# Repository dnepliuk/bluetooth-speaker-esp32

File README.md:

# bluetooth-speaker-esp32

Двошарова плата Bluetooth-колонки на ESP32, з ЦАП PCM5102A і підсилювачем TPA3116D2.

Відкрийте `BluetoothSpeaker.kicad_pro` у KiCad 10 зі стандартними бібліотеками символів, посадкових місць і 3D-моделей. Локальні бібліотеки зберігаються в `lib/`. Таблиці `sym-lib-table` та `fp-lib-table` посилаються на них відносно папки проєкту. Правила плати містяться в `BluetoothSpeaker.kicad_dru`.

Для механічного компонування доступна модель корпусу U7 у `lib/ul_TPA3116D2DAD/DAD0032A.stp`. PCB посилається на стандартні моделі KiCad для U7 та клемників J1/J3/J4. Якщо цих моделей немає в установленому наборі, відповідні корпуси можуть не відображатися у 3D.

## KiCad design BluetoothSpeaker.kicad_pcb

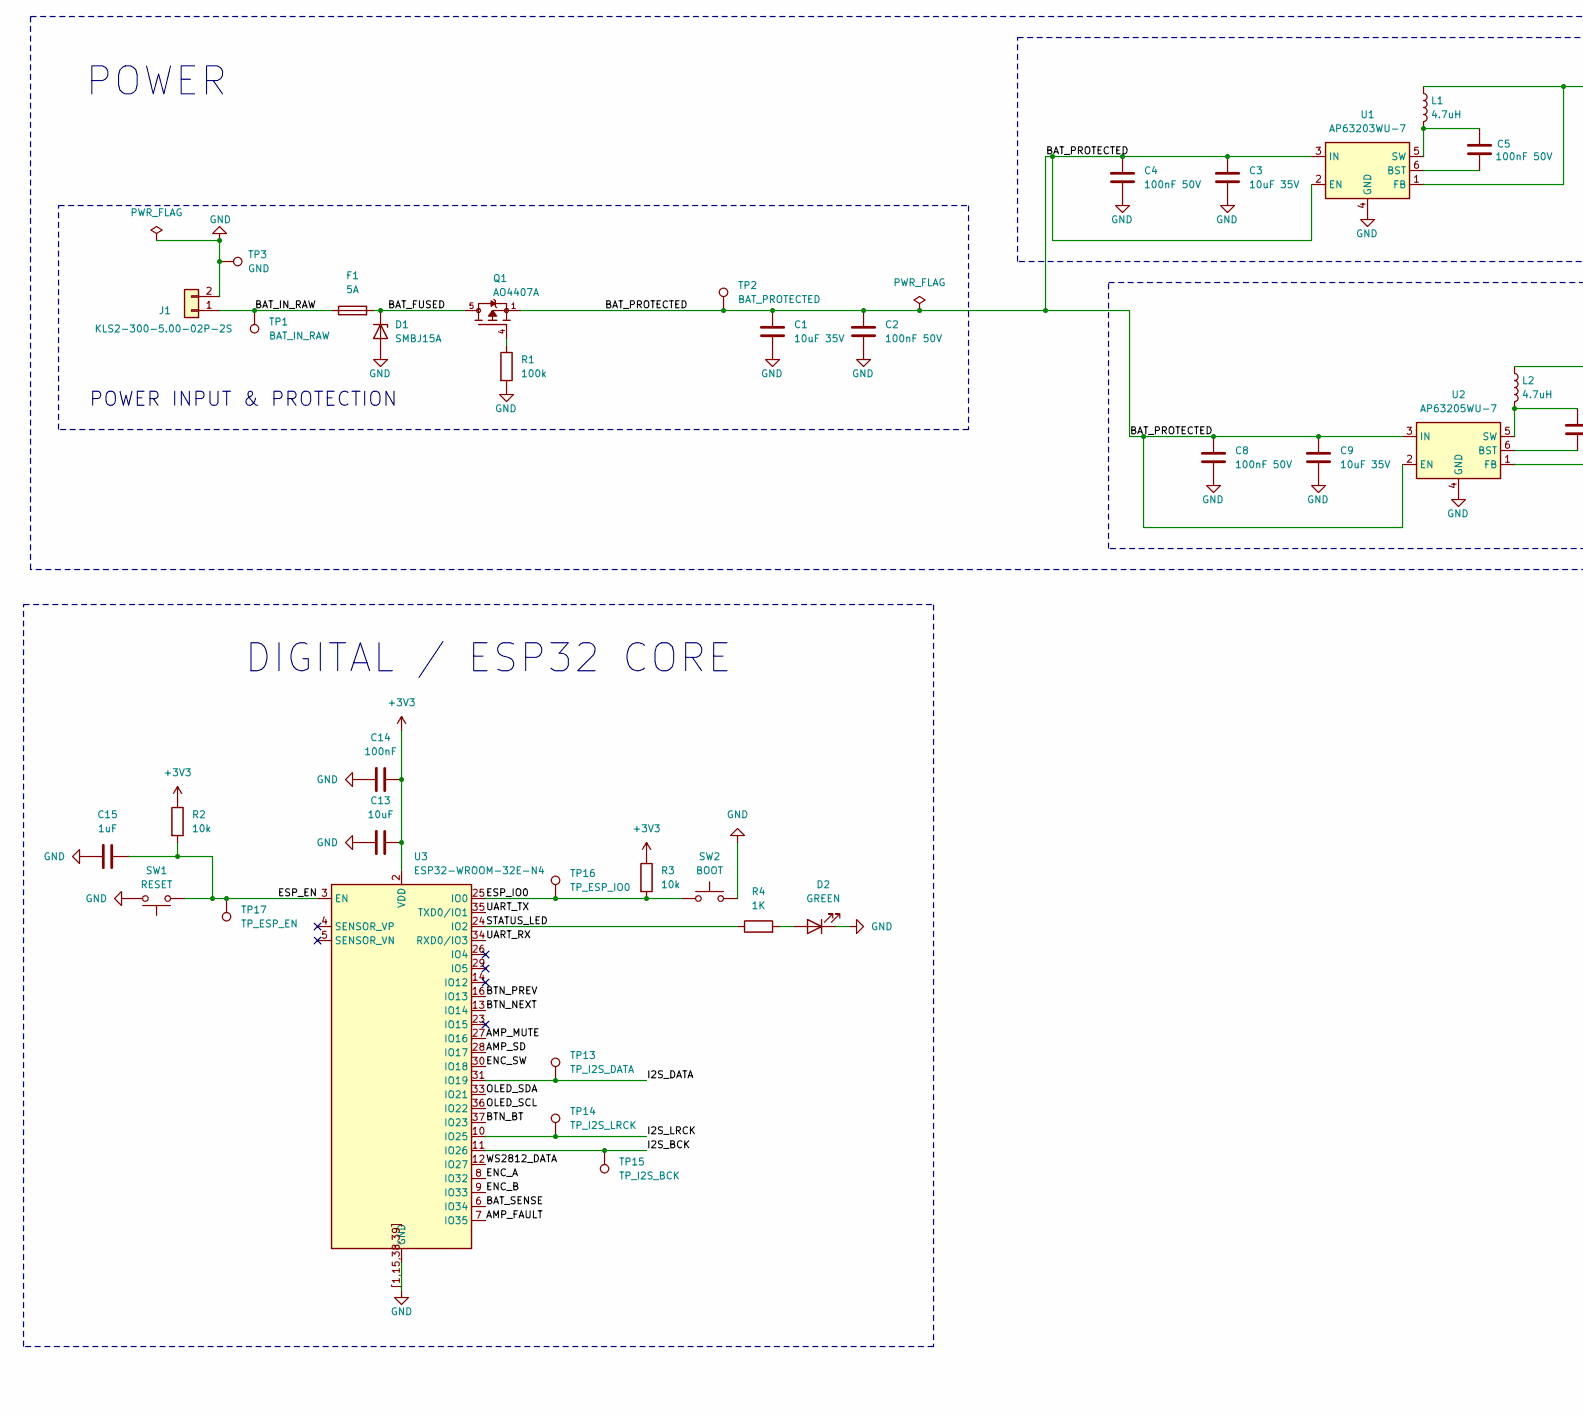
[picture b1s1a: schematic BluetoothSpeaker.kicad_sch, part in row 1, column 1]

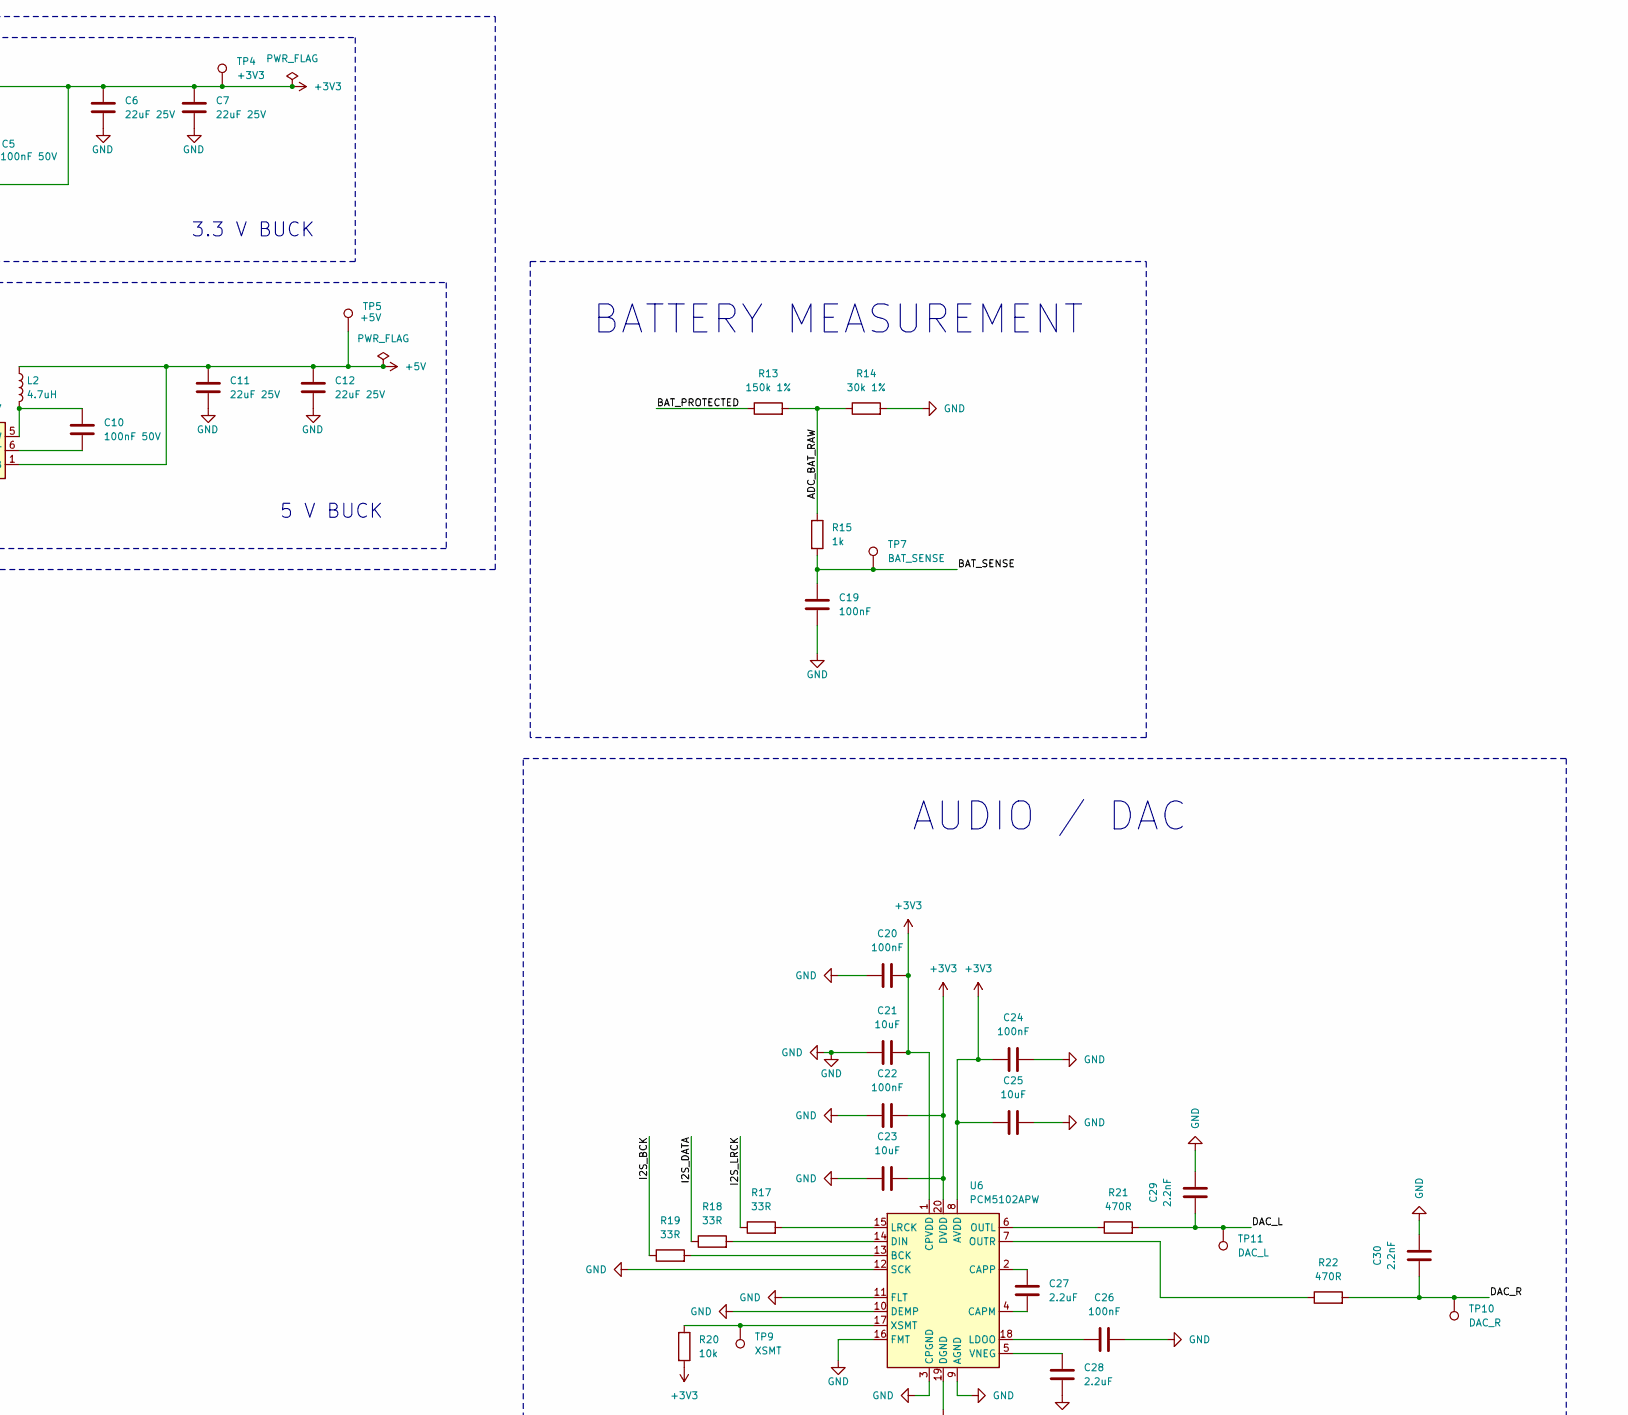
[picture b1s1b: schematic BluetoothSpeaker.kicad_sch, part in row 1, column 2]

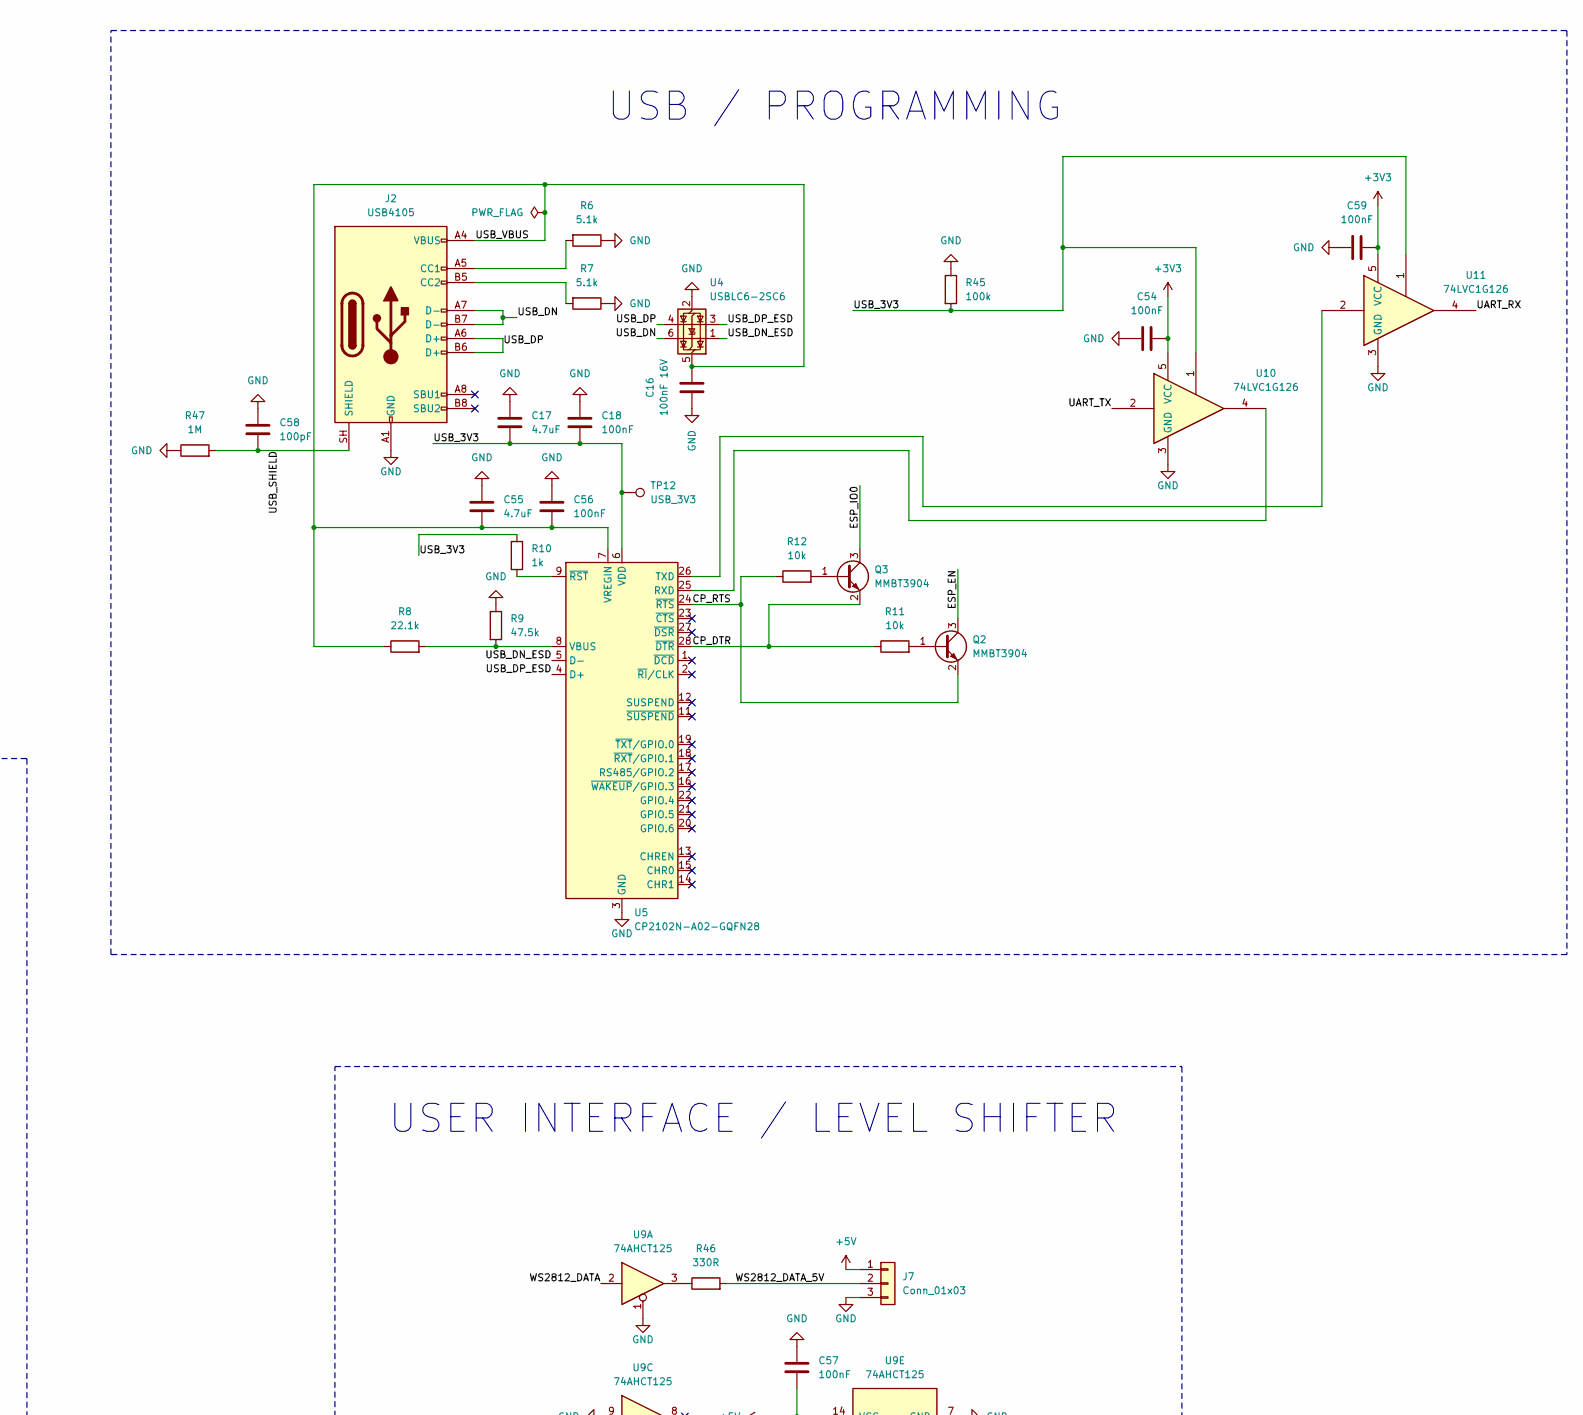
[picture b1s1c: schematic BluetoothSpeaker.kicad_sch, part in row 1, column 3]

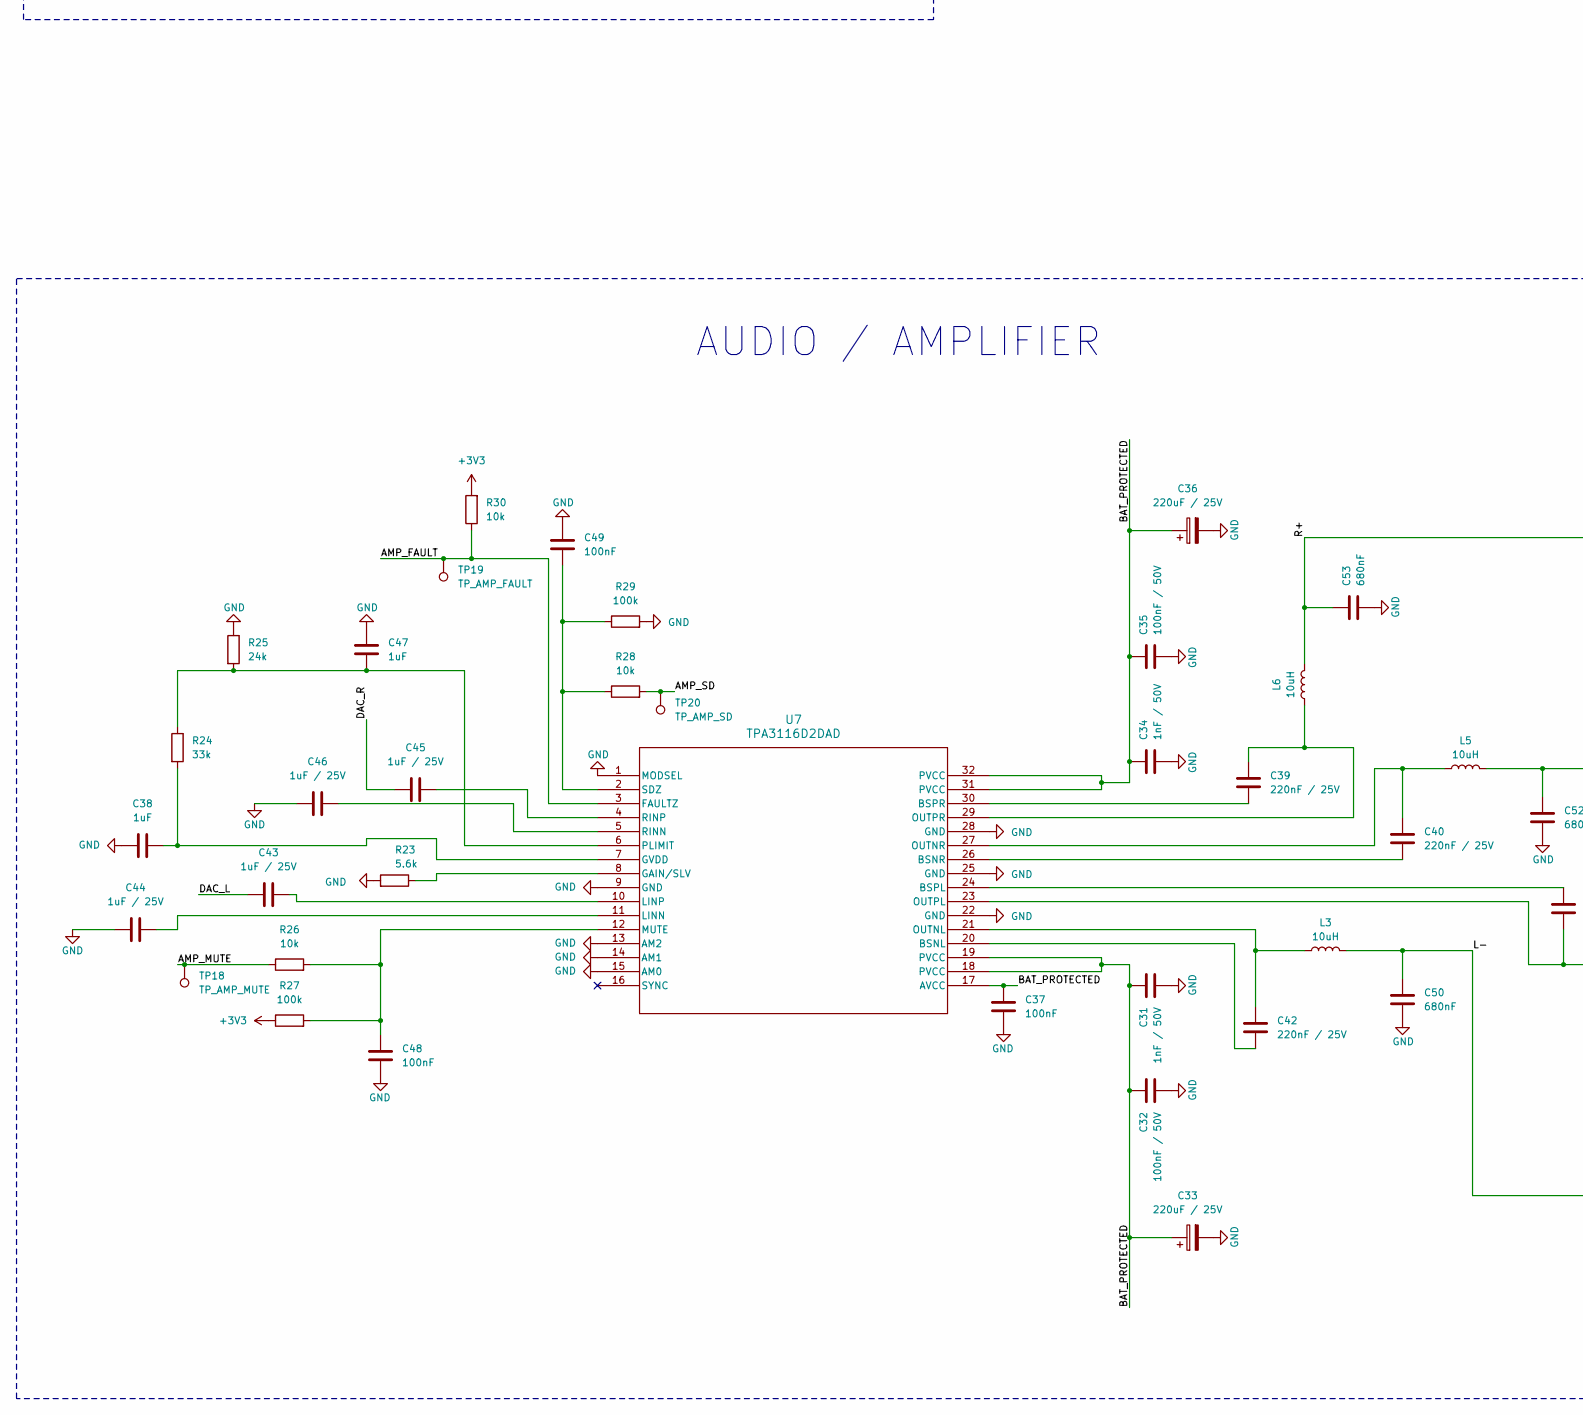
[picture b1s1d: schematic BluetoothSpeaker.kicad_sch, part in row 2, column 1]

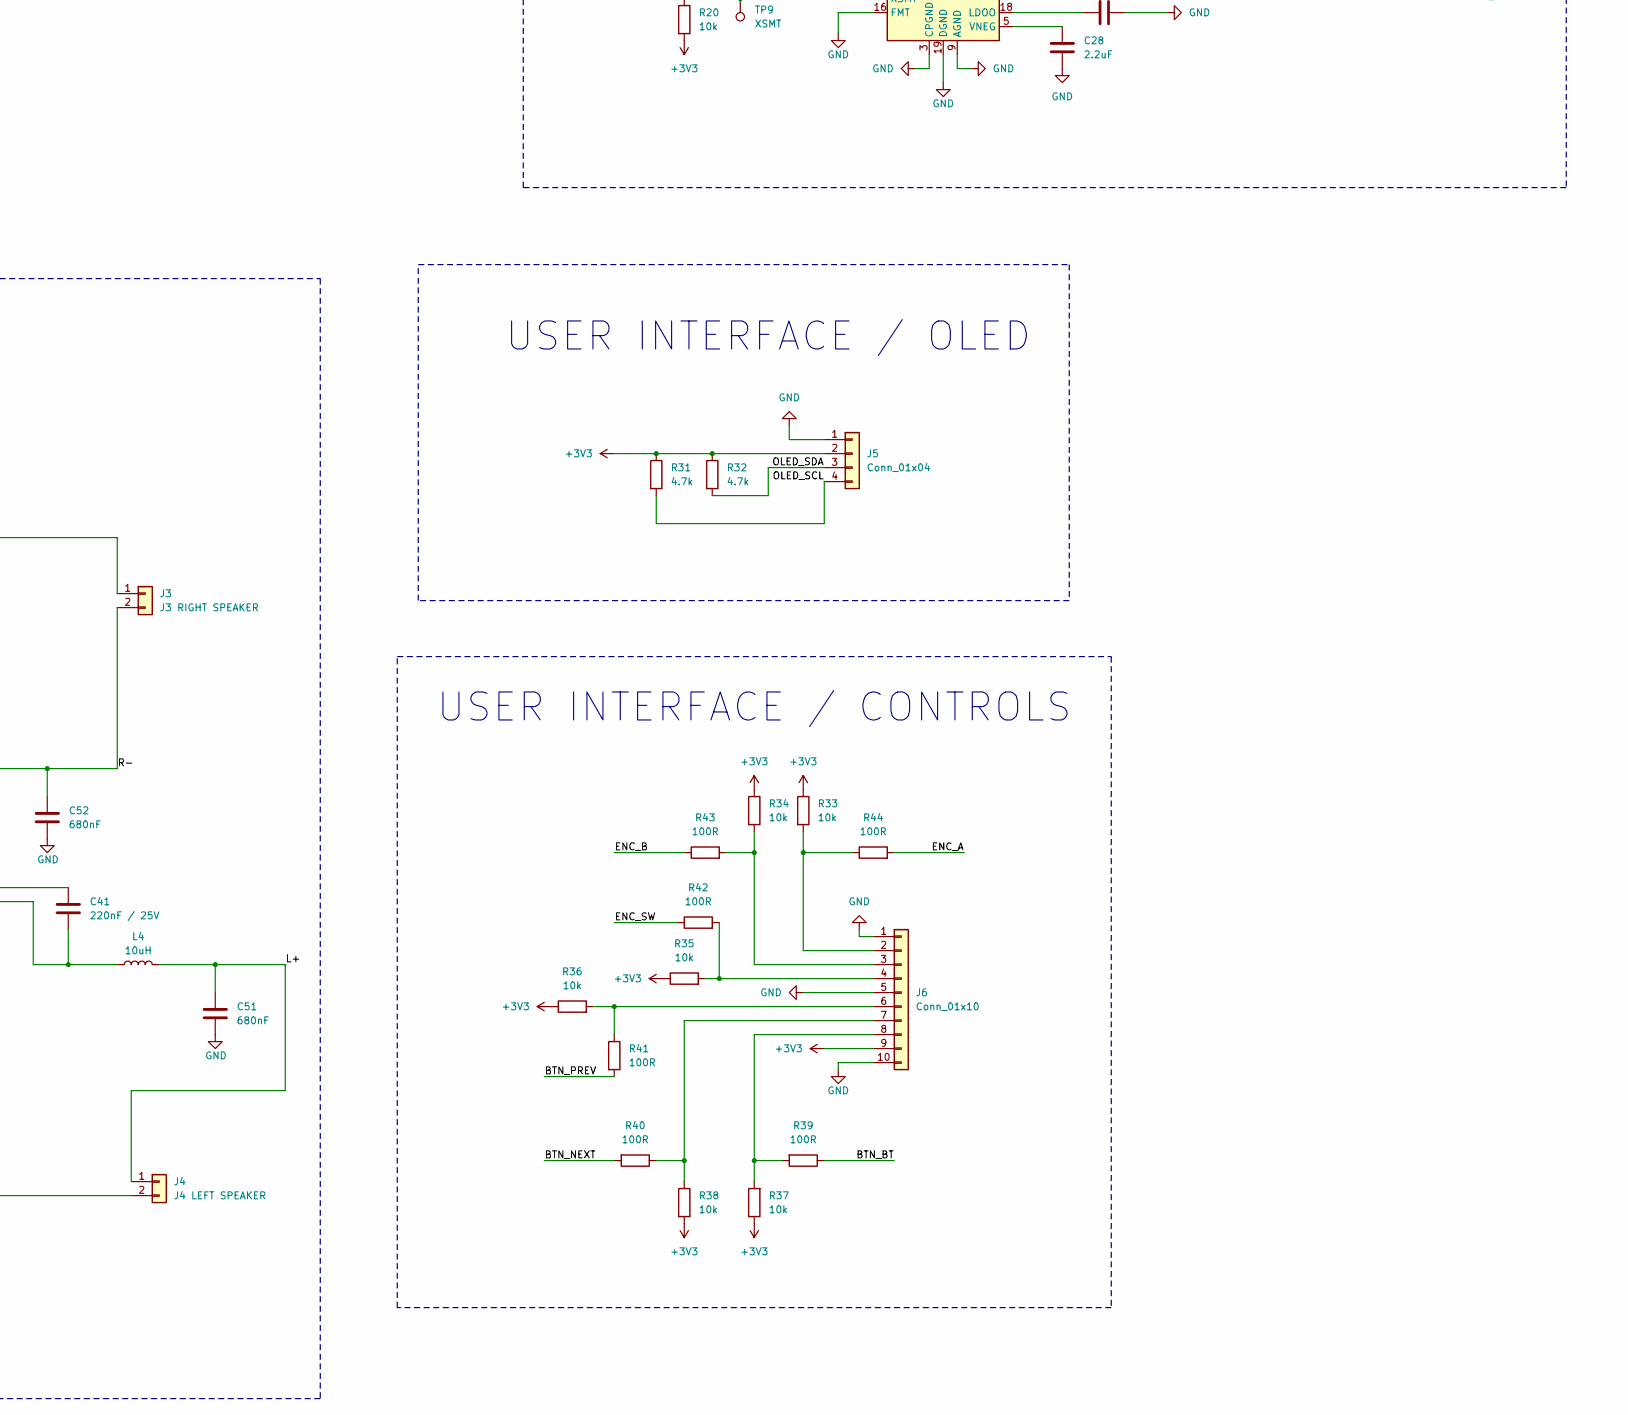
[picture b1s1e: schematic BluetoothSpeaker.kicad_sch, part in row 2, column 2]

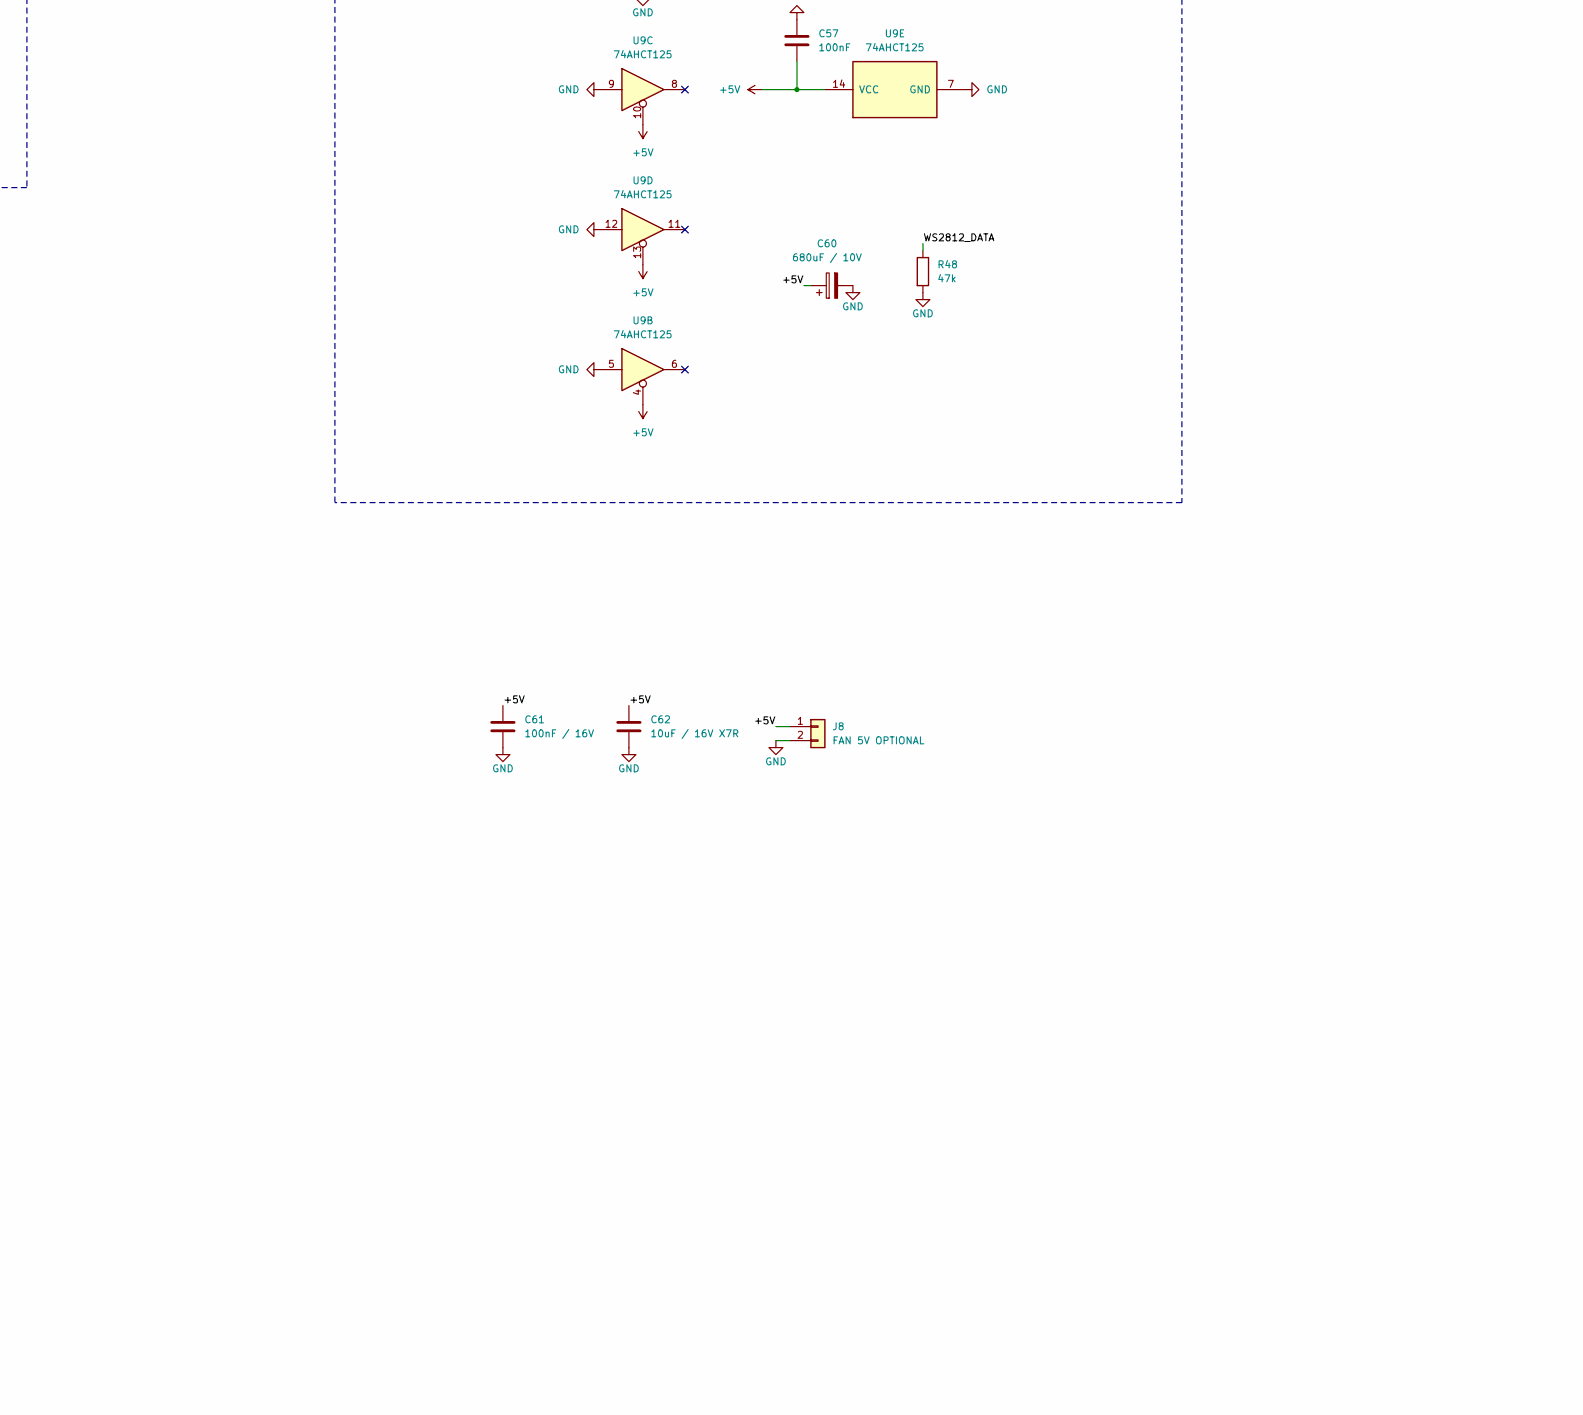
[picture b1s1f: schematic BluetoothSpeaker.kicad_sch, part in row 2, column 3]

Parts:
C1, C3, C9: 10uF 35V; C_1210_3225Metric
C2, C4, C5, C8, C10: 100nF 50V; C_0805_2012Metric
C6, C7, C11, C12: 22uF 25V; C_1210_3225Metric
C13, C21, C23, C25: 10uF; C_1206_3216Metric
C14, C18, C19, C20, C22, C24, C26, C37, C48, C49, C54, C56, C57, C59: 100nF; C_0805_2012Metric
C15, C38, C47: 1uF; C_0805_2012Metric
C16: 100nF 16V; C_0805_2012Metric
C17, C55: 4.7uF; C_0805_2012Metric
C27, C28: 2.2uF; C_0805_2012Metric
C29, C30: 2.2nF; C_0805_2012Metric
C31, C34: 1nF / 50V; C_0805_2012Metric
C32, C35: 100nF / 50V; C_0805_2012Metric
C33, C36: 220uF / 25V; CP_Radial_D8.0mm_P3.50mm
C39, C40, C41, C42: 220nF / 25V; C_0805_2012Metric
C43, C44, C45, C46: 1uF / 25V; C_0805_2012Metric
C50, C51, C52, C53: 680nF; C_1812_4532Metric
C58: 100pF; C_1206_3216Metric
C60: 680uF / 10V; CP_Radial_D8.0mm_P3.50mm
C61: 100nF / 16V; C_0805_2012Metric
C62: 10uF / 16V X7R; C_1206_3216Metric
D1: SMBJ15A; D_SMB
D2: GREEN; LED_0805_2012Metric
F1: 5A; C_1808_4520Metric
J1: KLS2-300-5.00-02P-2S; TerminalBlock_MaiXu_MX126-5.0-02P_1x02_P5.00mm
J2: USB4105; GCT_USB4105_JLC
J3: J3 RIGHT SPEAKER; TerminalBlock_MaiXu_MX126-5.0-02P_1x02_P5.00mm
J4: J4 LEFT SPEAKER; TerminalBlock_MaiXu_MX126-5.0-02P_1x02_P5.00mm
J5: Conn_01x04; PinHeader_1x04_P2.54mm_Vertical
J6: Conn_01x10; PinHeader_1x10_P2.54mm_Vertical
J7: Conn_01x03; PinHeader_1x03_P2.54mm_Vertical
J8: FAN 5V OPTIONAL; PinHeader_1x02_P2.54mm_Vertical
L1, L2: 4.7uH; L_Bourns_SRR1260
L3, L4, L5, L6: 10uH; L_Bourns_SRR1260
Q1: AO4407A; SOIC127P600X175-8N; PARTREV I
Q2, Q3: MMBT3904; SOT-23
R1, R27, R29, R45: 100k; R_0805_2012Metric
R2, R3, R11, R12, R20, R26, R28, R30, R33, R34, R35, R36, R37, R38: 10k; R_0805_2012Metric
R4: 1K; R_0805_2012Metric
R6, R7: 5.1k; R_0805_2012Metric
R8: 22.1k; R_0805_2012Metric
R9: 47.5k; R_0805_2012Metric
R10, R15: 1k; R_0805_2012Metric
R13: 150k 1%; R_0805_2012Metric
R14: 30k 1%; R_0805_2012Metric
R17, R18, R19: 33R; R_0805_2012Metric
R21, R22: 470R; R_0805_2012Metric
R23: 5.6k; R_0805_2012Metric
R24: 33k; R_0805_2012Metric
R25: 24k; R_0805_2012Metric
R31, R32: 4.7k; R_0805_2012Metric
R39, R40, R41, R42, R43, R44: 100R; R_0805_2012Metric
R46: 330R; R_0805_2012Metric
R47: 1M; R_0805_2012Metric
R48: 47k; R_0805_2012Metric
SW1: RESET; SW_PUSH_6mm
SW2: BOOT; SW_PUSH_6mm
TP1: BAT_IN_RAW; TestPoint_THTPad_D2.0mm_Drill1.0mm
TP2: BAT_PROTECTED; TestPoint_THTPad_D2.0mm_Drill1.0mm
TP3: GND; TestPoint_THTPad_D2.0mm_Drill1.0mm
TP4: +3V3; TestPoint_THTPad_D2.0mm_Drill1.0mm
TP5: +5V; TestPoint_THTPad_D2.0mm_Drill1.0mm
TP7: BAT_SENSE; TestPoint_THTPad_D2.0mm_Drill1.0mm
TP9: XSMT; TestPoint_THTPad_D2.0mm_Drill1.0mm
TP10: DAC_R; TestPoint_THTPad_D2.0mm_Drill1.0mm
TP11: DAC_L; TestPoint_THTPad_D2.0mm_Drill1.0mm
TP12: USB_3V3; TestPoint_THTPad_D2.0mm_Drill1.0mm
TP13: TP_I2S_DATA; TestPoint_THTPad_D2.0mm_Drill1.0mm
TP14: TP_I2S_LRCK; TestPoint_THTPad_D2.0mm_Drill1.0mm
TP15: TP_I2S_BCK; TestPoint_THTPad_D2.0mm_Drill1.0mm
TP16: TP_ESP_IO0; TestPoint_THTPad_D2.0mm_Drill1.0mm
TP17: TP_ESP_EN; TestPoint_THTPad_D2.0mm_Drill1.0mm
TP18: TP_AMP_MUTE; TestPoint_THTPad_D2.0mm_Drill1.0mm
TP19: TP_AMP_FAULT; TestPoint_THTPad_D2.0mm_Drill1.0mm
TP20: TP_AMP_SD; TestPoint_THTPad_D2.0mm_Drill1.0mm
U1: AP63203WU-7; TSOT-23-6
U2: AP63205WU-7; TSOT-23-6
U3: ESP32-WROOM-32E-N4; ESP32-WROOM-32E_Drill030
U4: USBLC6-2SC6; SOT-23-6
U5: CP2102N-A02-GQFN28; CP2102N_QFN28_EP
U6: PCM5102APW; TSSOP-20_4.4x6.5mm_P0.65mm
U7: TPA3116D2DAD; Texas_DAD0032A_HTSSOP-32_6.1x11mm_P0.65mm_TopEP3.71x3.81mm
U9: 74AHCT125; SOIC-14_3.9x8.7mm_P1.27mm
U10, U11: 74LVC1G126; SOT-353_SC-70-5

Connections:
+3V3: C6.1, C7.1, C13.2, C14.2, C20.2, C21.2, C22.2, C23.2, C24.1, C25.1, C54.1, C59.1, J5.2, J6.9, L1.1, R2.1, R3.1, R20.2, R27.1, R30.2, R31.1, R32.1, R33.1, R34.1, R35.1, R36.1, R37.1, R38.2, TP4.1 (1_1), U1.1 (FB), U3.2 (VDD), U6.1 (CPVDD), U6.8 (AVDD), U6.20 (DVDD), U10.5 (VCC), U11.5 (VCC)
+5V: C11.1, C12.1, C57.2, C60.1, C61.1, C62.1, J7.1, J8.1, L2.1, TP5.1 (1_1), U2.1 (FB), U9.4, U9.10, U9.13, U9.14 (VCC)
/ADC_BAT_RAW: R13.2, R14.1, R15.1
/AMP_FAULT: R30.1, TP19.1 (1_1), U3.7 (IO35), U7.3 (FAULTZ)
/AMP_MUTE: R26.1, TP18.1 (1_1), U3.27 (IO16)
/AMP_SD: R28.2, TP20.1 (1_1), U3.28 (IO17)
/BAT_FUSED: D1.1 (K), F1.2, Q1.5, Q1.6, Q1.7, Q1.8
/BAT_IN_RAW: F1.1, J1.1, TP1.1 (1_1)
/BAT_PROTECTED: C1.1, C2.1, C3.1, C4.2, C8.1, C9.1, C31.1, C32.1, C33.1, C34.1, C35.1, C36.1, C37.1, Q1.1, Q1.2, Q1.3, R13.1, TP2.1 (1_1), U1.2 (EN), U1.3 (IN), U2.2 (EN), U2.3 (IN), U7.17 (AVCC), U7.18 (PVCC), U7.19 (PVCC), U7.31 (PVCC), U7.32 (PVCC)
/BAT_SENSE: C19.1, R15.2, TP7.1 (1_1), U3.6 (IO34)
/BTN_BT: R39.1, U3.37 (IO23)
/BTN_NEXT: R40.2, U3.13 (IO14)
/BTN_PREV: R41.2, U3.16 (IO13)
/CP_DTR: Q3.2 (E), R11.1, U5.28 (~DTR)
/CP_RTS: Q2.2 (E), R12.1, U5.24 (~RTS)
/DAC_L: C29.2, C43.1, R21.2, TP11.1 (1_1)
/DAC_R: C30.1, C45.1, R22.2, TP10.1 (1_1)
/ENC_A: R44.2, U3.8 (IO32)
/ENC_B: R43.1, U3.9 (IO33)
/ENC_SW: R42.1, U3.30 (IO18)
/ESP_EN: C15.1, Q2.3 (C), R2.2, SW1.1, TP17.1 (1_1), U3.3 (EN)
/ESP_IO0: Q3.3 (C), R3.2, SW2.1, TP16.1 (1_1), U3.25 (IO0)
/I2S_BCK: R19.1, TP15.1 (1_1), U3.11 (IO26)
/I2S_DATA: R18.1, TP13.1 (1_1), U3.31 (IO19)
/I2S_LRCK: R17.1, TP14.1 (1_1), U3.10 (IO25)
/L+: C51.1, J4.1, L4.2
/L-: C50.1, J4.2, L3.2
/OLED_SCL: J5.4, R31.2, U3.36 (IO22)
/OLED_SDA: J5.3, R32.2, U3.33 (IO21)
/R+: C53.1, J3.1, L6.2
/R-: C52.1, J3.2, L5.2
/STATUS_LED: R4.1, U3.24 (IO2)
/UART_RX: U3.34 (RXD0/IO3), U11.4
/UART_TX: U3.35 (TXD0/IO1), U10.2
/USB_3V3: C17.2, C18.2, R10.2, R45.2, TP12.1 (1_1), U5.6 (VDD), U10.1, U11.1
/USB_DN: J2.A7 (D-), J2.B7 (D-), U4.6 (I/O1)
/USB_DN_ESD: U4.1 (I/O1), U5.5 (D-)
/USB_DP: J2.A6 (D+), J2.B6 (D+), U4.4 (I/O2)
/USB_DP_ESD: U4.3 (I/O2), U5.4 (D+)
/USB_SHIELD: C58.2, J2.SH (SHIELD), R47.2
/USB_VBUS: C16.1, C55.2, C56.2, J2.A4 (VBUS), J2.A9 (VBUS), J2.B4 (VBUS), J2.B9 (VBUS), R8.1, U4.5 (VBUS), U5.7 (VREGIN)
/WS2812_DATA: R48.1, U3.12 (IO27), U9.2
/WS2812_DATA_5V: J7.2, R46.2
GND: C1.2, C2.2, C3.2, C4.1, C6.2, C7.2, C8.2, C9.2, C11.2, C12.2, C13.1, C14.1, C15.2, C16.2, C17.1, C18.1, C19.2, C20.1, C21.1, C22.1, C23.1, C24.2, C25.2, C26.2, C28.2, C29.1, C30.2, C31.2, C32.2, C33.2, C34.2, C35.2, C36.2, C37.2, C38.1, C44.1, C46.1, C47.1, C48.2, C49.1, C50.2, C51.2, C52.2, C53.2, C54.2, C55.1, C56.1, C57.1, C58.1, C59.2, C60.2, C61.2, C62.2, D1.2 (A), D2.1 (K), J1.2, J2.A1 (GND), J2.A12 (GND), J2.B1 (GND), J2.B12 (GND), J5.1, J6.1, J6.5, J6.10, J7.3, J8.2, R1.2, R6.1, R7.1, R9.1, R14.2, R23.2, R25.1, R29.2, R45.1, R47.1, R48.2, SW1.2, SW2.2, TP3.1 (1_1), U1.4 (GND), U2.4 (GND), U3.1 (GND), U3.15 (GND), U3.38 (GND), U3.39 (GND), U3.[1,15,38,39] (GND), U4.2 (GND), U5.3 (GND), U5.29 (GND), U6.3 (CPGND), U6.9 (AGND), U6.10 (DEMP), U6.11 (FLT), U6.12 (SCK), U6.16 (FMT), U6.19 (DGND), U7.1 (MODSEL), U7.9 (GND), U7.13 (AM2), U7.14 (AM1), U7.15 (AM0), U7.22 (GND), U7.25 (GND), U7.28 (GND), U9.1, U9.5, U9.7 (GND), U9.9, U9.12, U10.3 (GND), U11.3 (GND)
unnamed: D2.2 (A), R4.2
unnamed: J2.A5 (CC1), R6.2
unnamed: J2.B5 (CC2), R7.2
unnamed: J6.2, R33.2, R44.1
unnamed: J6.3, R34.2, R43.2
unnamed: J6.4, R35.2, R42.2
unnamed: J6.6, R36.2, R41.1
unnamed: J6.7, R38.1, R40.1
unnamed: J6.8, R37.2, R39.2
unnamed: Q1.4, R1.1
unnamed: Q2.1 (B), R11.2
unnamed: Q3.1 (B), R12.2
unnamed: R46.1, U9.3
unnamed: C5.2, U1.6 (BST)
unnamed: C5.1, L1.2, U1.5 (SW)
unnamed: C10.2, U2.6 (BST)
unnamed: C10.1, L2.2, U2.5 (SW)
unnamed: U5.25 (RXD), U10.4
unnamed: U5.26 (TXD), U11.2
unnamed: R8.2, R9.2, U5.8 (VBUS)
unnamed: R10.1, U5.9 (~RST)
unnamed: R19.2, U6.13 (BCK)
unnamed: C27.2, U6.4 (CAPM)
unnamed: C27.1, U6.2 (CAPP)
unnamed: R18.2, U6.14 (DIN)
unnamed: C26.1, U6.18 (LDOO)
unnamed: R17.2, U6.15 (LRCK)
unnamed: R21.1, U6.6 (OUTL)
unnamed: R22.1, U6.7 (OUTR)
unnamed: C28.1, U6.5 (VNEG)
unnamed: R20.1, TP9.1 (1_1), U6.17 (XSMT)
unnamed: C42.2, U7.20 (BSNL)
unnamed: C40.2, U7.26 (BSNR)
unnamed: C41.1, U7.24 (BSPL)
unnamed: C39.2, U7.30 (BSPR)
unnamed: R23.1, U7.8 (GAIN/SLV)
unnamed: C38.2, R24.2, U7.7 (GVDD)
unnamed: C44.2, U7.11 (LINN)
unnamed: C43.2, U7.10 (LINP)
unnamed: C48.1, R26.2, R27.2, U7.12 (MUTE)
unnamed: C42.1, L3.1, U7.21 (OUTNL)
unnamed: C40.1, L5.1, U7.27 (OUTNR)
unnamed: C41.2, L4.1, U7.23 (OUTPL)
unnamed: C39.1, L6.1, U7.29 (OUTPR)
unnamed: C47.2, R24.1, R25.2, U7.6 (PLIMIT)
unnamed: C46.2, U7.5 (RINN)
unnamed: C45.2, U7.4 (RINP)
unnamed: C49.2, R28.1, R29.1, U7.2 (SDZ)

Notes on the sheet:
3.3 V BUCK
AUDIO / DAC
USB / PROGRAMMING
USER INTERFACE / OLED
USER INTERFACE / CONTROLS
5 V BUCK
USER INTERFACE / LEVEL SHIFTER
DIGITAL / ESP32 CORE
AUDIO / AMPLIFIER
BATTERY MEASUREMENT
POWER INPUT & PROTECTION
POWER

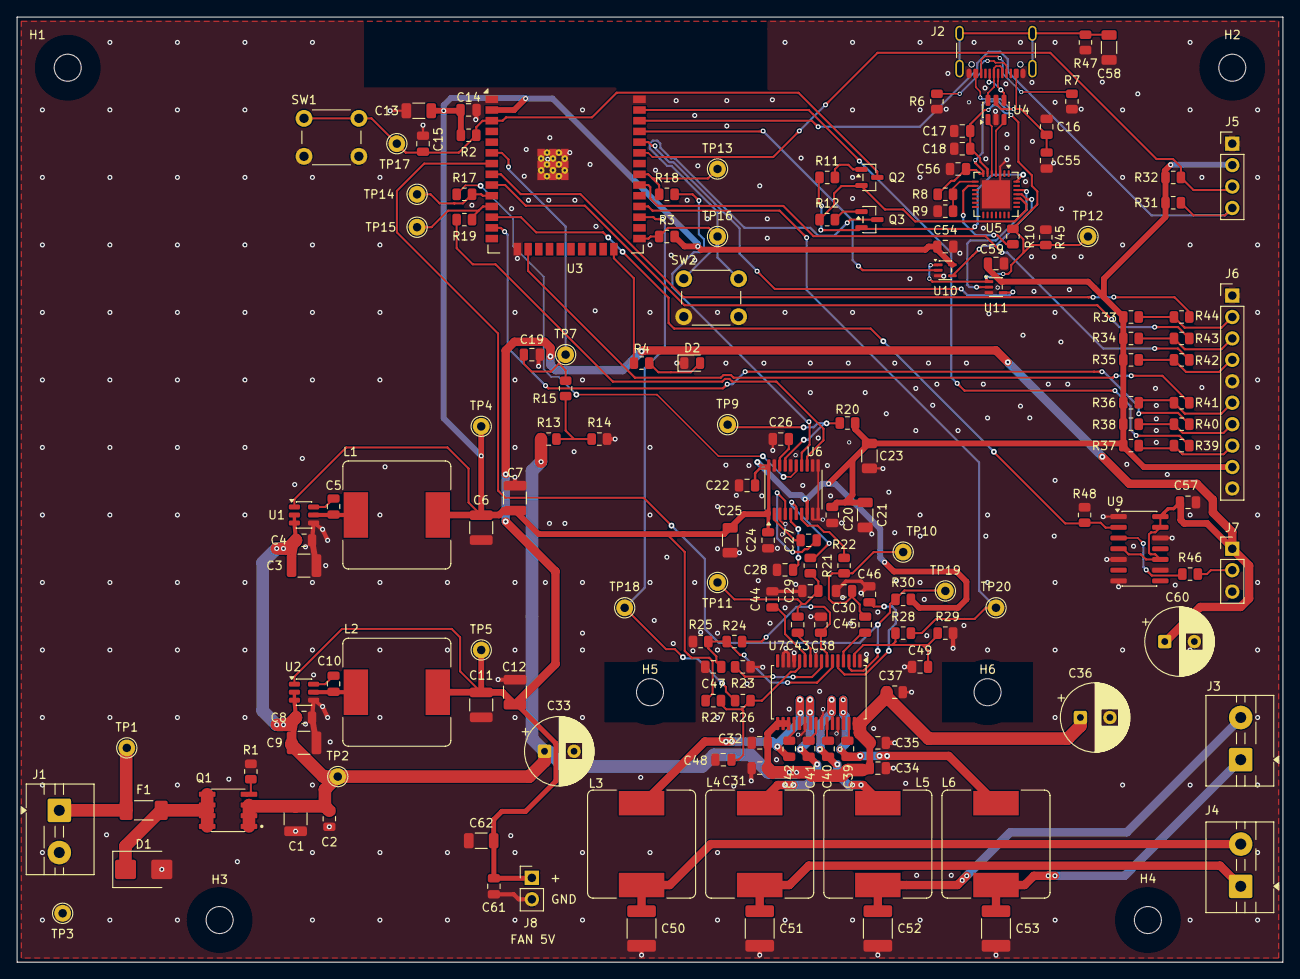
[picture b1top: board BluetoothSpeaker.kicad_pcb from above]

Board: 2 copper layers, 150.0 x 112.0 mm, 164 parts (0 on the bottom side), 92 nets.

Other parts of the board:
H1, H2, H3, H4: MountingHole; MountingHole_3.2mm_M3
H5, H6: ATS #4-40 clearance 3.2mm; MountingHole_3.2mm_M3
